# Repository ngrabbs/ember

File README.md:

# EMBER

**Emission Monitoring for Burn Event Recognition** is a Mississippi State ECE
capstone project building a CubeSat-class wildfire detection instrument and
ground station. Its narrowband cameras look for the potassium emission
signature of flaming vegetation.

## System at a glance

[Editable diagrams.net source](docs/architecture/ember-system.drawio)

The camera payload processes images locally. The IHU passes fire-check results
and housekeeping telemetry to Yamcs over the UHF link. The EPS supplies the onboard electronics over
a separate power bus. The optional Walter path carries LTE-M telemetry, and
the direct IHU USB link supports wired bench operation.

## Hardware and firmware

Running versions are the latest recorded bench identities. Where a separate
development version is undocumented, the table gives the source version on `main`.

| Hardware | Revision or status | Bench firmware | Firmware development |
|---|---|---|---|
| [Electrical power system](hardware/eps/README.md) | Rev A prototype · Rev B in design | IHU reads the charger over I²C | Rev B STM32 supervision planned |
| [Solar panel](hardware/pv_panel/README.md) | Rev D design and release files | — | — |
| [Housekeeping computer](hardware/ihu/README.md) | RP2040 CAN Feather prototype | [IHU `0.32.0`](firmware/ihu/releases/0.32.0/README.md) | [`main` `0.34.0`](firmware/ihu/VERSION) |
| [UHF transceiver](hardware/comms/README.md) | Y24 prototype with original Pico | [Transceiver `0.41.0`](firmware/transceiver/releases/0.41.0/README.md) | [`main` `0.41.0`](firmware/transceiver/VERSION) |
| [Camera payload](https://github.com/ngrabbs/koenig_wildfire) | Three-camera prototype on Pi 4 | [Payload `0.7.1`](firmware/payload/README.md) | [`main` `0.8.0`](firmware/payload/VERSION) |
| [Jetson carrier](hardware/payload_compute/README.md) | Next prototype in design | — | — |
| [Walter LTE-M bench](ground/lte/README.md) | CAN Feather and Walter modem | Last recorded `0.8.0` Feather · `0.3.0` Walter | `main` `0.14.1` Walter MCU · `0.3.0` Walter |
| [Ground station](ground/README.md) | Pi 5 and LibreSDR bench | [EMBER ground `1.9.1`](ground/releases/yamcs-flight-1.9.1.json) | [Ground releases](ground/releases/README.md) |
| [S-band transmitter](hardware/payload_exp_sband_tx/README.md) | Experimental FPGA bench | FPGA test designs | [FPGA work](hardware/payload_exp_sband_tx/fpga/README.md) |

[Hardware directory](hardware/README.md) · [Firmware guides](firmware/README.md) ·
[Radio guide](docs/comms/README.md) · [System architecture](docs/architecture/README.md)

## Team

Austin Burris (Housekeeping), William Ball (Power), Nick Grabbs
(Communications), Dustin Johnson (Command & Telemetry), and Jacob Timmons
(Payload).

Advisors are Dr. Dillon Boyd and Dr. Keith Koenig.

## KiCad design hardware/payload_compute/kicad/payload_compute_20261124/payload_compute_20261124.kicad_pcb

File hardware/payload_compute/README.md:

# Payload Hardware

## Layout

- `design/`: payload design concepts and constraints
- `kicad/`: KiCad projects, including the converted Altium carrier
- `altium/`, `altium-carlos/`: local-only Altium sources — **not tracked**
- `bringup/`: validation plans and logs
- `releases/`: build-ready release packages

## Board source status

Open the [November 24 PAYLOAD compute project](kicad/payload_compute_20261124/payload_compute_20261124.kicad_pro) for the current placement and routing work. It uses the EPS-switched VBAT feed, local 5 V and 3.3 V converters, and CAN A for the Jetson shutdown request. The project includes its custom symbols, footprints, and connector STEP models.

### Earlier prototype

The [earlier prototype project](kicad/payload_compute_rev_next/payload_compute_rev_next.kicad_pro)
now contains the root hierarchy, AON supply, reset/run core, three limited
reverse-blocking bootstrap feeds, startup mode/source locks, live IHU
permission and external watchdog/reset qualification. Raw-source and main-bus
qualification, USB PD and main admissions remain upcoming capture stages.
The source-choice outputs do not yet establish safe power admission.
See [stage evidence and open boundaries](kicad/payload_compute_rev_next/README.md).
Review the [current six-sheet schematic PDF](kicad/payload_compute_rev_next/payload_compute_rev_next-stage3.pdf).

Use the [next-carrier schematic baseline](design/schematic_start.md):
power/source control, STM32 dual CAN, module/camera interfaces, debug and
portable-bench operation are defined for staged prototype capture. The
converted carrier remains a reference, not the accepted new circuit.

See the [preliminary power budget](design/power_budget.md) for input-power
estimates, proposed local rails, USB-C PD options, and measurement gates.
The [power architecture](design/power_architecture.md) develops the input
protection, regulator shortlist, USB bootstrap, source selection, and
sequencing behavior. It remains a circuit proposal pending detailed design.
The [eFuse package acceptance](design/efuse_library_acceptance.md) now records
all ten physical leads, a disposable placement and separate copper/stencil
renders. The [USB admission study](design/admission_control.md) now contains
a wired input circuit and raw-powered enable clamp. Its exported topology
passes; temperature, low-state leakage and ramps remain unqualified.
The [AON supply budget](design/aon_supply_budget.py) replaces the earlier ±2%
assumption with the preferred PFM regulator's asymmetric DC allocation;
startup and transient qualification remain open. The
[AON regulator study](design/aon_regulator.md) now has an accepted prototype
package map, a standalone schematic and zero-error/warning ERC. Both new
circuits remain outside the carrier.
The [component sizing study](design/power_component_sizing.md) adds regulator
passives, protection threshold corners, and separate USB/battery qualification
profiles, with a [reproducible calculator](design/power_sizing.py).
The [disposable 5 V circuit study](design/validation/payload_power_acceptance/README.md)
now has a schematic, render, exported topology, and zero-error/warning ERC.
The [regulator library acceptance record](design/lmr51460_library_acceptance.md)
documents corrected footprint geometry and passed library acceptance after
the local Konnect repair. This circuit has not been integrated into the carrier.
It recommends evaluating 15 V / 3 A PD for full lab operation; this supersedes
the earlier fixed-9-V proposal as the preferred candidate, pending acceptance
and validation. Regulator candidates are shortlisted; the battery bank and
final regulator qualification remain open.
The [power-control contract and monitor screening](design/power_control.md)
records the accepted IHU hard-kill semantics, a fault-cleared run latch,
module I/O discharge constraints and unresolved 5 V monitoring margins.
Its [executable study](design/power_control_study.py) checks ideal logic and
DC divider corners; it does not qualify the hardware timing.
The [precision monitor budget](design/precision_monitor.md) uses
REF3425IDBVR plus LM2903BIDR. Their [physical pin maps](design/monitor_library_acceptance.md)
are accepted, and the [disposable monitor circuit](design/validation/payload_monitor_acceptance/README.md)
has passed ERC and exact exported-connectivity checks. Its DC corners pass
the allocated limits; regulator transients, passive selection and hardware
timing still require qualification. The scratch feedback divider
uses 10 kΩ / 1.91 kΩ to reduce leakage error at the same nominal voltage.

The [run-latch/startup study](design/run_latch.md) now has an AON reset supervisor,
separate converter gates and a fault-cleared latch, with accepted package maps
and checked exported connectivity. Four upstream electrical boundaries remain
unimplemented and are recorded in ERC. Module level interfaces, bench-mode
sampling and rail discharge are the next circuit blocks. NVIDIA guide v1.5
supersedes the preliminary local startup timing evidence.

The [bench-mode sampler](design/bench_mode.md) now locks the physical jumper
until AON reset and preserves it through ordinary STM32 resets. Its disposable
schematic has checked connectivity and one declared external-reset ERC error.
PAYLOAD_EN is proposed as 3.3 V push-pull, default low, per the user selection;
the IHU receiver and mode/source permission logic now have a checked
standalone circuit study; source-admission hardware remains open.

The [IHU receiver and permission proposal](design/permission_control.md)
checks 512 combinations, includes both-source rejection and default-low IHU
reception, and preserves fresh-arm recovery. Its disposable KiCad schematic
is wired and its exported topology passes all 512 combinations. NAND package
acceptance is complete. ERC retains one external-reset error and two boundary
warnings. See the [study evidence](design/validation/payload_permission_acceptance/README.md).
The PCB is a package-validation scratch board; carrier integration is pending.

The [source-selection study](design/source_selection.md) now separates AON
bootstrap from the three default-off main paths, defines immutable startup
source choice and independent source-health feedback, and checks 32,768
admission combinations. It revises USB main UV/OV screens and identifies
the battery current-limit and bootstrap-budget gaps. Source switches, their
fail-off interfaces remain to be implemented. The new project's AON supply
and bootstrap feeds are captured; see the
[bootstrap input/restart contract](design/bootstrap_input_contract.md) and
[exact bootstrap package acceptance](design/bootstrap_library_acceptance.md).

### Payload compute requirements discussion — 2026-10-04

These requirements describe the next revision. The converted schematic and
PCB have not yet been updated or validated against them; older pin-map and
schematic-guide assumptions must be reconciled during implementation.

Accepted mission and operating requirements:

- Capture and retain three spectral images, process them onboard for wildfire
  detection, and report compact results to the IHU. Channels use 750, 770,
  and 780 nm filters. Capture cadence and regional observation windows remain
  experimental, with battery usage a principal constraint.
- Target the existing Jetson Orin Nano module and retain intended compatibility
  with the team's older Nano modules using separate software builds. Exact
  module identities, storage arrangements, and interface compatibility still
  require verification.
- Use microSD storage; do not add an NVMe SSD interface.
- Retain captures in a bounded rolling store: overwrite the oldest ordinary
  captures when needed and protect wildfire detections within a reserved
  storage budget. Reserve operating-system/free-space headroom. Define the
  protected-store-full behavior, quotas, and retention of raw/processed data
  before implementation; protected captures cannot grow without bound.
- Retain the three original raw frames and processing results for each stored
  capture, with JPEG previews for the bench web interface.
- Use the Koenig payload's three global-shutter cameras. Its current hardware
  documentation identifies InnoMaker CAM-IMX296RAW, which differs from the
  Raspberry Pi camera-board assumption in the existing carrier pin map.
  Confirm exact camera hardware before accepting connector or trigger wiring.
- All camera testing so far has used a Pi 4. The hardware-trigger attempt with
  the Arducam mux did not work. Simultaneous exposure and successful receipt
  of all three frames remain validation goals on the new carrier.
- Provide a removable M.2 Wi-Fi module for standalone bench operation and the
  Koenig web-interface workflow. Flight operation omits the Wi-Fi module.
- Preserve automatic Wi-Fi access-point fallback from the Koenig workflow:
  join a configured network when available; otherwise host an access point
  for laptop access without requiring command-line setup. Verify this behavior
  with the selected Wi-Fi card and each supported Jetson software image.
- Preserve mounting provisions and clearance for the ground-test fan and heat
  spreader. Provide the same mating fan interface as the Orin Nano devkit.
  NVIDIA's connector correction identifies ACES 50275-00471-003, four pins,
  1.25 mm pitch. Confirm physical mating, pin numbering, supply/current,
  PWM/tach electrical interfaces, and footprint before accepting a part.
  The compact flight thermal/mechanical arrangement remains unresolved;
  retaining a fan connector does not establish a flight cooling solution.
- Target JLCPCB fabrication. Assembly scope and exact parts remain open.

Accepted control and power architecture:

- Add an STM32 supervisor with two built-in CAN controllers and separate
  external transceivers for stack CAN A and CAN B. Exact MCU/package and
  failover behavior remain open; STM32G0B1 is an initial candidate only.
- IHU authorizes observation sessions and supplies capture parameters and
  schedules. STM32 generates scheduled hardware triggers after Jetson reports
  the cameras armed; also support a single-capture command. Sessions are
  bounded by duration and/or capture count.
- Jetson owns camera configuration, image acquisition, storage, processing,
  and the bench web interface. STM32 owns CAN communication, power sequencing,
  trigger timing, and watchdog recovery.
- Provide a standalone bench power connector for the nominal 6.0–8.4 V
  battery range. A 12 V adapter input is not required. Bench/stack source
  selection, protection, and local peripheral supplies remain to be designed.
- Provide a bench-mode jumper: with bench mode selected at startup, valid
  standalone power automatically boots Jetson and the web interface. Stack
  mode waits for IHU authorization. Define mode sampling and source selection
  so a fitted jumper cannot accidentally override flight controls.
- Keep the supervisor available while board power is present, with the Jetson
  and associated payload loads on a switched domain. Reconcile this with the
  existing direct PAYLOAD_EN-to-buck connection and stack-powered peripherals.
- Request graceful shutdown and allow image writes to finish before normal
  power removal. Normal stops use CAN while IHU retains permission;
  PAYLOAD_EN low is an immediate hardware kill and may interrupt SD writes.
  STM32 may power-cycle an unresponsive Jetson using bounded
  retries, report recovery events to IHU, and defer repeated-failure policy
  to IHU. Timeouts and retry counts remain open.

Student-lab power/access baseline:

- Preferred USB-C PD input: 15 V / 3 A through protected independent bootstrap
  and main paths, locally regulated to 5 V for Jetson. USB 5 V powers supervision
  only. Exact bank/cable qualification and actual attach/load budget remain open.
- The suggested Adafruit 4288 USB-A 5 V / 2.1 A bank is not selected for full
  payload operation. Do not parallel its outputs.
- A startup-sampled bench jumper enables automatic boot and Koenig Wi-Fi AP
  fallback. Provide ready/fault indication, web/button graceful stop, and no
  insufficient-power boot loop. Source choice locks until AON power cycle.
- STM32 owns two CAN paths, explicit-direction application UART, hardware
  trigger/strobe timing, power sequencing and independent watchdog recovery.
  Jetson and MCU have separate console access; MCU also has SWD.
- Camera trigger circuitry uses the exact InnoMaker optocoupler/header revision;
  triple Jetson acquisition and Jetson trigger driver support remain validation
  gates. Detailed contracts and open hardware gates are in the baseline above.

`kicad/cubesat_orin_nano_carrier` is the converted Jetson Orin Nano carrier:
87 footprints, a flat 4-page schematic (root + `Cameras`, `M2_USB_UART`,
`SODIMM_Power`), 650 track segments — mostly the PCIe escape from J1. Board
design in this repo is KiCad-only per
[`hardware/conventions/kicad_jlcpcb_design_rules.md`](../conventions/kicad_jlcpcb_design_rules.md);
the Altium trees are kept locally as the conversion source and are ignored by
git (see the Altium block in the root `.gitignore`).

## Mechanical — CSKB / PC/104 envelope

The outline, mounting holes and H1/H2 positions are held **identical** to
`AMSAT/sdrb/hardware/pcb-variants/sdrb-cskb`, which is the reference that was
corrected to spec. Geometry is that board's Edge.Cuts translated by
`(+14.6103, -16.3164)` mm into this board's frame, so the two match exactly.

- Outline: 24 primitives, one closed loop, every endpoint used exactly twice,
  **95.8850 x 90.1800 mm**. X is exactly the CSK Slot1 profile; Y is 0.010 mm
  over the spec's 90.170, matching the reference.
- Mounting holes, inset from the nearest edges:

  | | left | right | top | bottom |
  | --- | --- | --- | --- | --- |
  | MH1 | 90.8050 | **5.0800** | **5.0900** | 85.0900 |
  | MH2 | **5.0800** | 90.8050 | 7.6300 | 82.5500 |
  | MH3 | **5.0800** | 90.8050 | 81.2900 | 8.8900 |
  | MH4 | 90.8050 | **5.0800** | 85.1000 | **5.0800** |

- CSKB connectors: H1 pin 1 at `(113.2136, 136.1236)`, H2 pin 1 at
  `(108.1336, 136.1236)`, both rotation -90. Pad rows sit **5.0800 / 7.6200 /
  10.1600 / 12.7000 mm** from the left board edge — the same four values as the
  reference. H1 to H2 pitch is 5.08 mm (0.2").

A bad outline fails silently — KiCad falls back to the bounding box and fab
output loses the notches. Re-run the closed-loop check after any outline edit.

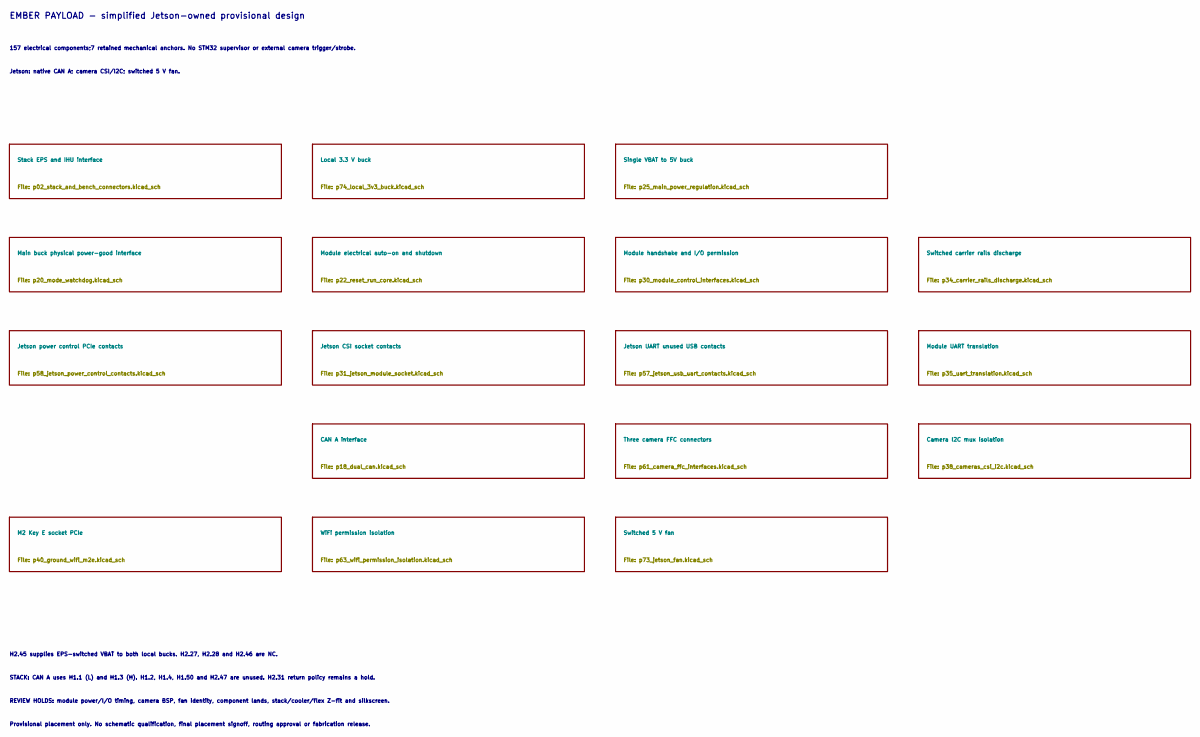
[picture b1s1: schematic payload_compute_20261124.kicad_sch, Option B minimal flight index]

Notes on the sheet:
EMBER PAYLOAD - simplified Jetson-owned provisional design
H2.45 supplies EPS-switched VBAT to both local bucks. H2.27, H2.28 and H2.46 are NC.
Jetson: native CAN A; camera CSI/I2C; switched 5 V fan.
157 electrical components;7 retained mechanical anchors. No STM32 supervisor or external camera trigger/strobe.
STACK: CAN A uses H1.1 (L) and H1.3 (H). H1.2, H1.4, H1.50 and H2.47 are unused. H2.31 return policy remains a hold.
Provisional placement only. No schematic qualification, final placement signoff, routing approval or fabrication release.
REVIEW HOLDS: module power/I/O timing, camera BSP, fan identity, component lands, stack/cooler/flex Z-fit and silkscreen.
